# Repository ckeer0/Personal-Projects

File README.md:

# Personal-Projects
All things that don't fit into other repos.

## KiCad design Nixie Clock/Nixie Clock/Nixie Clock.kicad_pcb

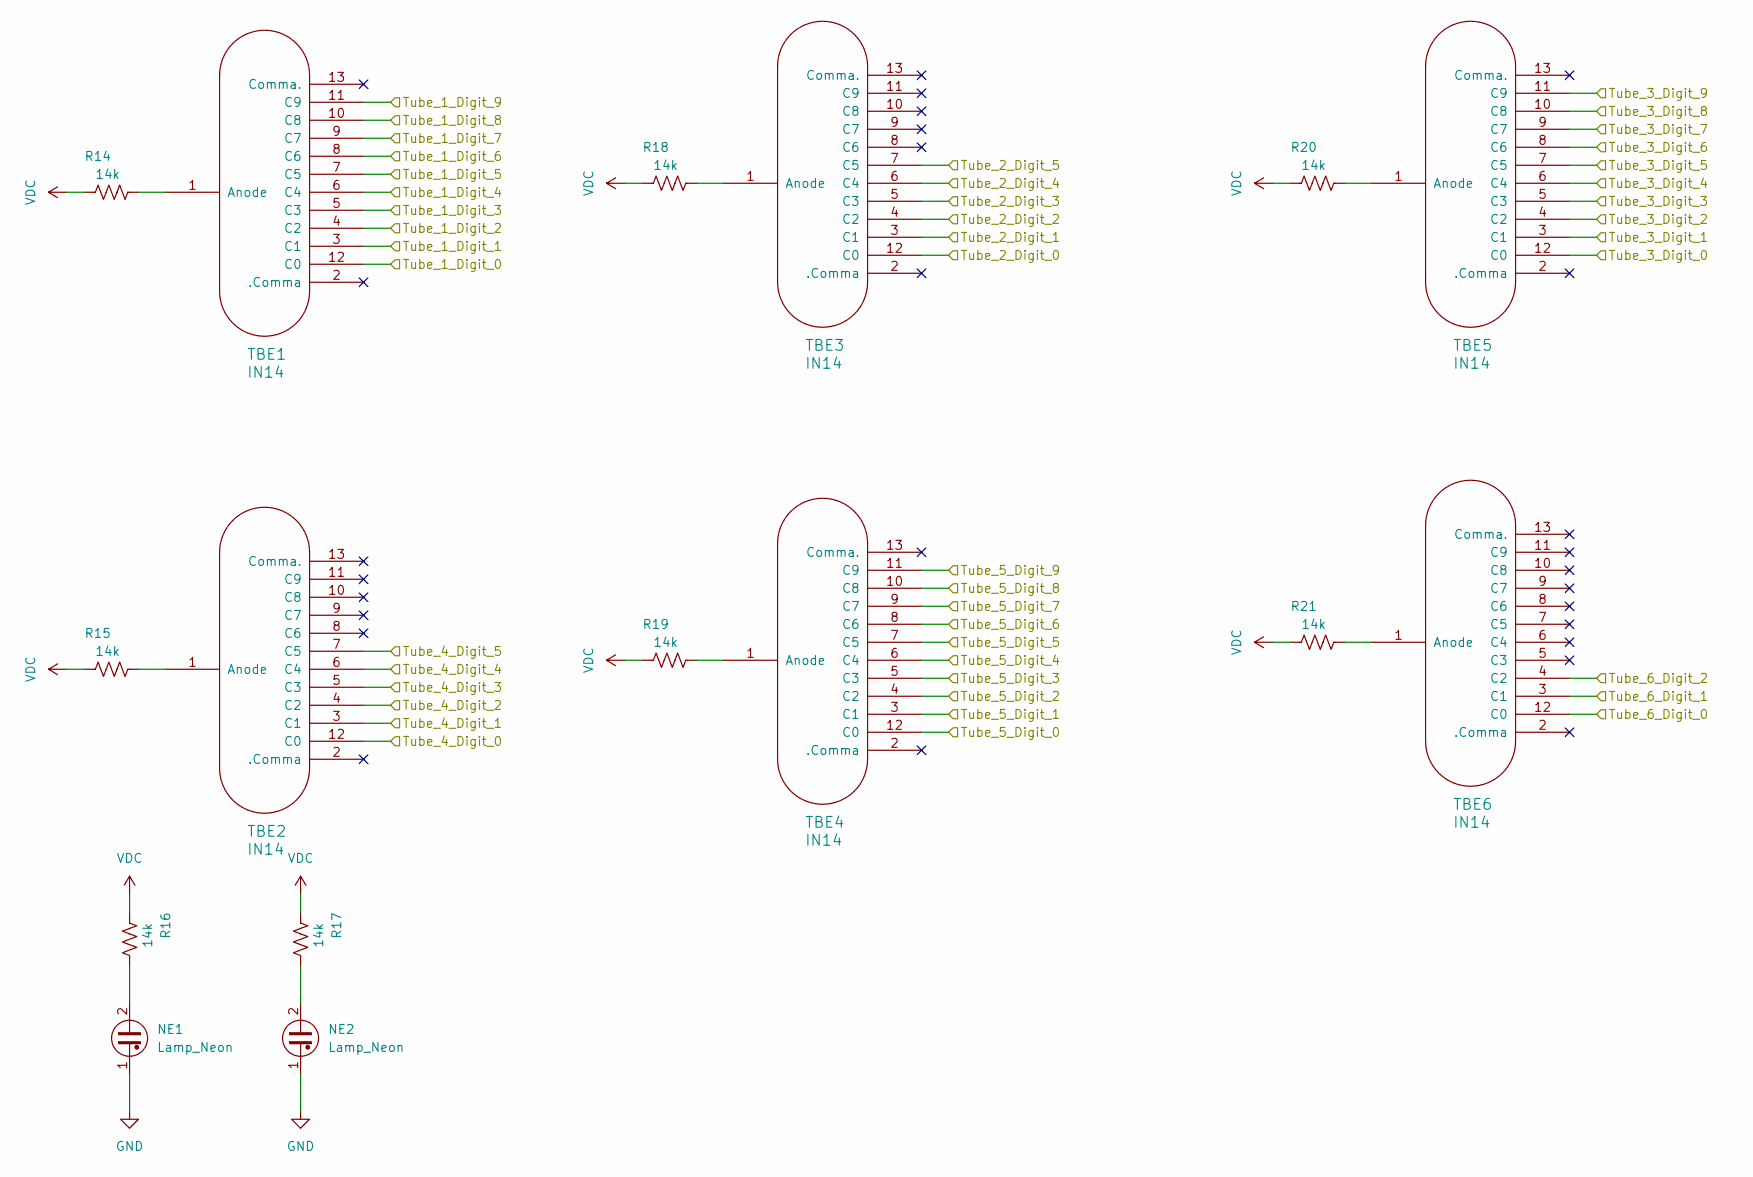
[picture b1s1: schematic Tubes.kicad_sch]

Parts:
NE1, NE2: Lamp_Neon; LED_D5.0mm_Clear
R14, R15, R18, R19, R20, R21: 14k; R_Axial_DIN0204_L3.6mm_D1.6mm_P7.62mm_Horizontal
R16, R17: 14k; R_Axial_DIN0207_L6.3mm_D2.5mm_P10.16mm_Horizontal
TBE1, TBE2, TBE3, TBE4, TBE5, TBE6: IN14; IN-14-mod

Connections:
/Tube_1_Digit_0: TBE1.12 (C0); also elsewhere on the board
/Tube_1_Digit_1: TBE1.3 (C1); also elsewhere on the board
/Tube_1_Digit_2: TBE1.4 (C2); also elsewhere on the board
/Tube_1_Digit_3: TBE1.5 (C3); also elsewhere on the board
/Tube_1_Digit_4: TBE1.6 (C4); also elsewhere on the board
/Tube_1_Digit_5: TBE1.7 (C5); also elsewhere on the board
/Tube_1_Digit_6: TBE1.8 (C6); also elsewhere on the board
/Tube_1_Digit_7: TBE1.9 (C7); also elsewhere on the board
/Tube_1_Digit_8: TBE1.10 (C8); also elsewhere on the board
/Tube_1_Digit_9: TBE1.11 (C9); also elsewhere on the board
/Tube_2_Digit_0: TBE3.12 (C0); also elsewhere on the board
/Tube_2_Digit_1: TBE3.3 (C1); also elsewhere on the board
/Tube_2_Digit_2: TBE3.4 (C2); also elsewhere on the board
/Tube_2_Digit_3: TBE3.5 (C3); also elsewhere on the board
/Tube_2_Digit_4: TBE3.6 (C4); also elsewhere on the board
/Tube_2_Digit_5: TBE3.7 (C5); also elsewhere on the board
/Tube_3_Digit_0: TBE5.12 (C0); also elsewhere on the board
/Tube_3_Digit_1: TBE5.3 (C1); also elsewhere on the board
/Tube_3_Digit_2: TBE5.4 (C2); also elsewhere on the board
/Tube_3_Digit_3: TBE5.5 (C3); also elsewhere on the board
/Tube_3_Digit_4: TBE5.6 (C4); also elsewhere on the board
/Tube_3_Digit_5: TBE5.7 (C5); also elsewhere on the board
/Tube_3_Digit_6: TBE5.8 (C6); also elsewhere on the board
/Tube_3_Digit_7: TBE5.9 (C7); also elsewhere on the board
/Tube_3_Digit_8: TBE5.10 (C8); also elsewhere on the board
/Tube_3_Digit_9: TBE5.11 (C9); also elsewhere on the board
/Tube_4_Digit_0: TBE2.12 (C0); also elsewhere on the board
/Tube_4_Digit_1: TBE2.3 (C1); also elsewhere on the board
/Tube_4_Digit_2: TBE2.4 (C2); also elsewhere on the board
/Tube_4_Digit_3: TBE2.5 (C3); also elsewhere on the board
/Tube_4_Digit_4: TBE2.6 (C4); also elsewhere on the board
/Tube_4_Digit_5: TBE2.7 (C5); also elsewhere on the board
/Tube_5_Digit_0: TBE4.12 (C0); also elsewhere on the board
/Tube_5_Digit_1: TBE4.3 (C1); also elsewhere on the board
/Tube_5_Digit_2: TBE4.4 (C2); also elsewhere on the board
/Tube_5_Digit_3: TBE4.5 (C3); also elsewhere on the board
/Tube_5_Digit_4: TBE4.6 (C4); also elsewhere on the board
/Tube_5_Digit_5: TBE4.7 (C5); also elsewhere on the board
/Tube_5_Digit_6: TBE4.8 (C6); also elsewhere on the board
/Tube_5_Digit_7: TBE4.9 (C7); also elsewhere on the board
/Tube_5_Digit_8: TBE4.10 (C8); also elsewhere on the board
/Tube_5_Digit_9: TBE4.11 (C9); also elsewhere on the board
/Tube_6_Digit_0: TBE6.12 (C0); also elsewhere on the board
/Tube_6_Digit_1: TBE6.3 (C1); also elsewhere on the board
/Tube_6_Digit_2: TBE6.4 (C2); also elsewhere on the board
GND: NE1.1, NE2.1; also elsewhere on the board
unnamed: NE1.2, R16.1
unnamed: NE2.2, R17.1
unnamed: R14.1, TBE1.1 (Anode)
unnamed: R15.1, TBE2.1 (Anode)
unnamed: R18.1, TBE3.1 (Anode)
unnamed: R19.1, TBE4.1 (Anode)
unnamed: R20.1, TBE5.1 (Anode)
unnamed: R21.1, TBE6.1 (Anode)
VDC: R14.2, R15.2, R16.2, R17.2, R18.2, R19.2, R20.2, R21.2; also elsewhere on the board

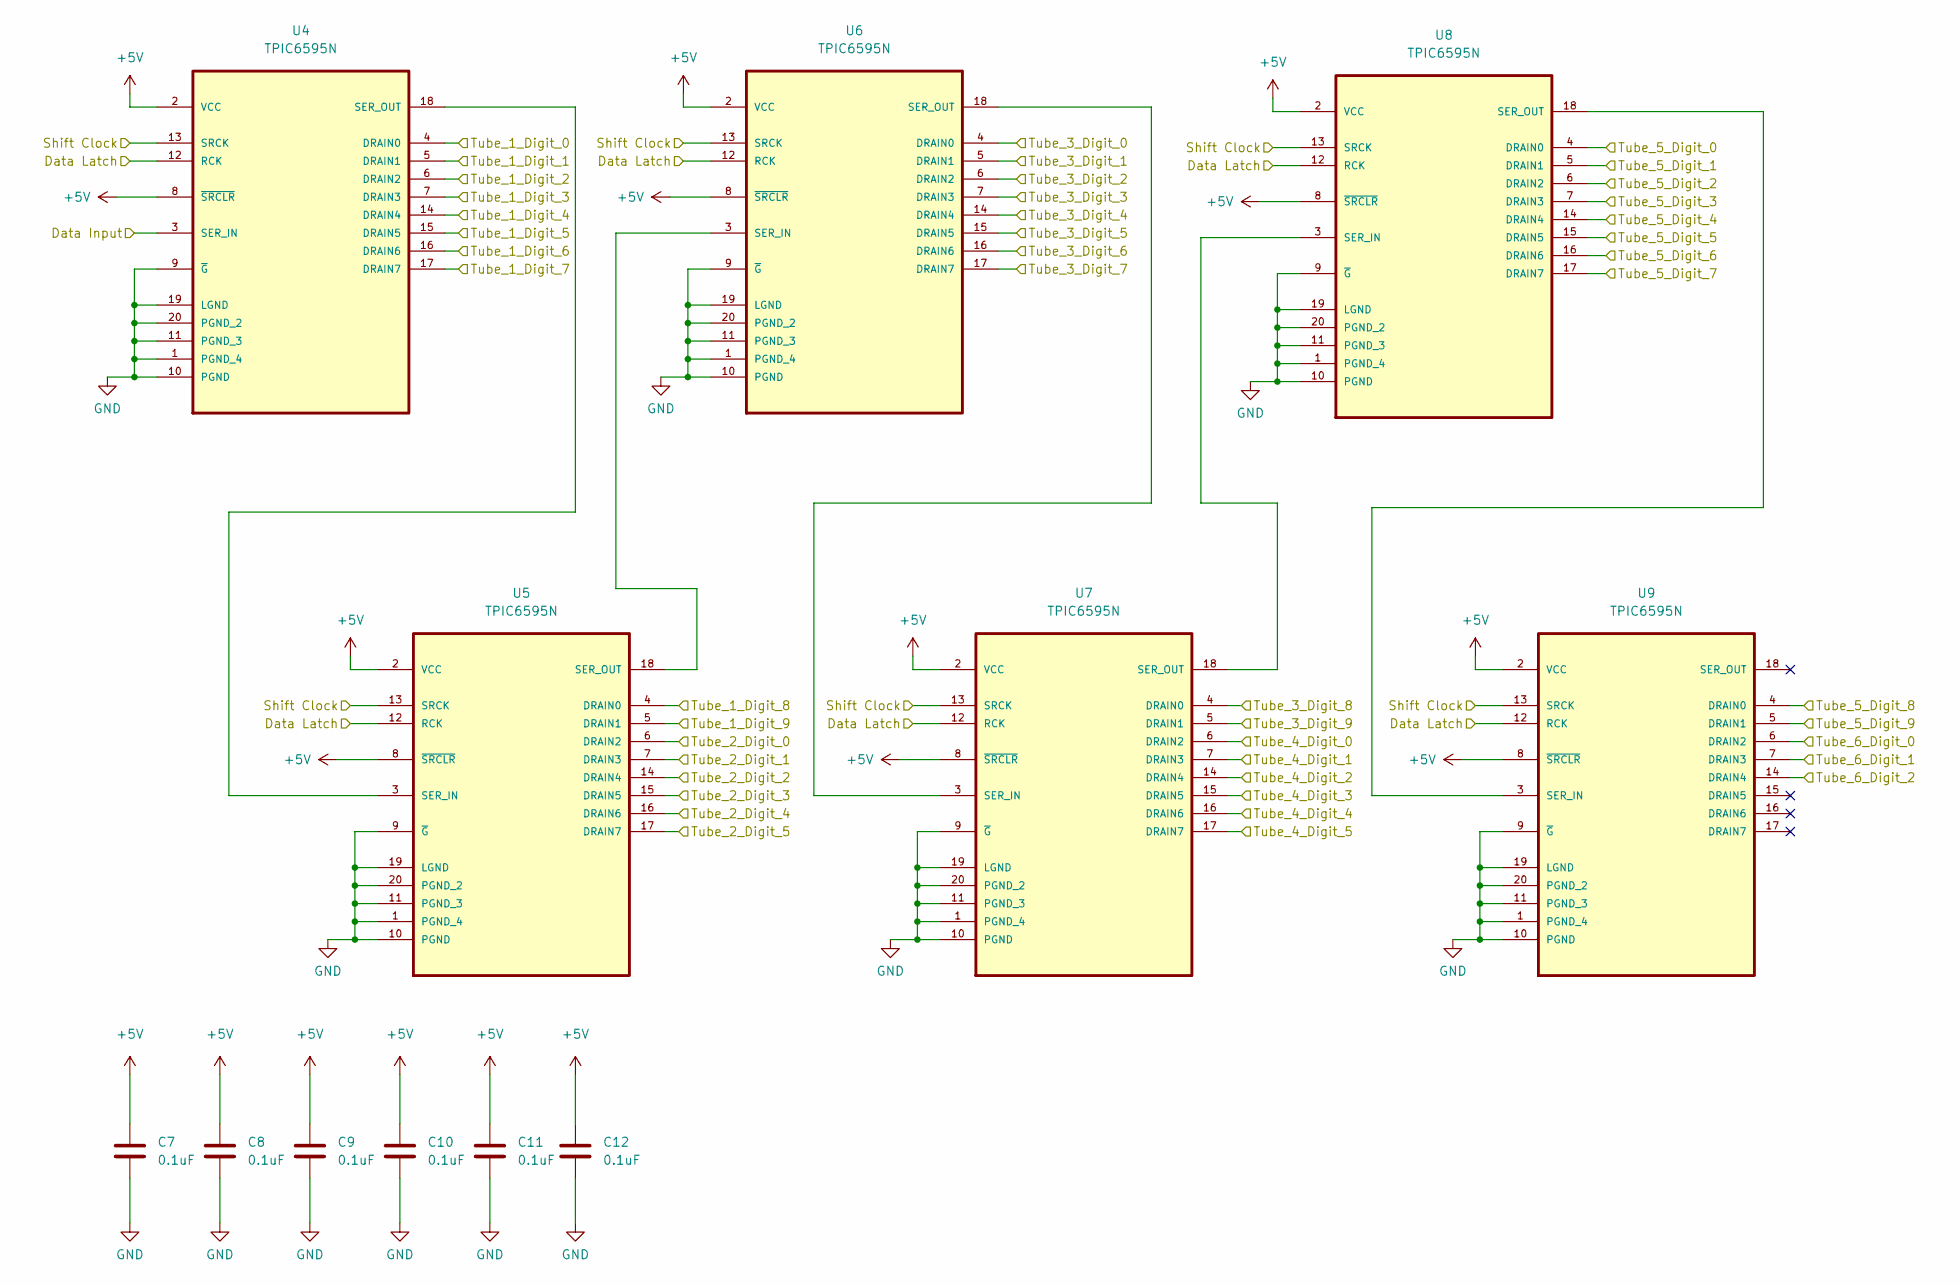
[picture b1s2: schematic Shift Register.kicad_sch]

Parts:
C7, C8, C9, C10, C11, C12: 0.1uF; CP_Radial_D4.0mm_P1.50mm
U4, U5, U6, U7, U8, U9: TPIC6595N; DIP254P762X508-20; MPN TPIC6595N

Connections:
+5V: C7.1, C8.1, C9.1, C10.1, C11.1, C12.1, U4.2 (VCC), U4.8 (~SRCLR), U5.2 (VCC), U5.8 (~SRCLR), U6.2 (VCC), U6.8 (~SRCLR), U7.2 (VCC), U7.8 (~SRCLR), U8.2 (VCC), U8.8 (~SRCLR), U9.2 (VCC), U9.8 (~SRCLR); also elsewhere on the board
/Data Latch: U4.12 (RCK), U5.12 (RCK), U6.12 (RCK), U7.12 (RCK), U8.12 (RCK), U9.12 (RCK); also elsewhere on the board
/Data Output: U4.3 (SER_IN); also elsewhere on the board
/Shift Clock: U4.13 (SRCK), U5.13 (SRCK), U6.13 (SRCK), U7.13 (SRCK), U8.13 (SRCK), U9.13 (SRCK); also elsewhere on the board
/Tube_1_Digit_0: U4.4 (DRAIN0); also elsewhere on the board
/Tube_1_Digit_1: U4.5 (DRAIN1); also elsewhere on the board
/Tube_1_Digit_2: U4.6 (DRAIN2); also elsewhere on the board
/Tube_1_Digit_3: U4.7 (DRAIN3); also elsewhere on the board
/Tube_1_Digit_4: U4.14 (DRAIN4); also elsewhere on the board
/Tube_1_Digit_5: U4.15 (DRAIN5); also elsewhere on the board
/Tube_1_Digit_6: U4.16 (DRAIN6); also elsewhere on the board
/Tube_1_Digit_7: U4.17 (DRAIN7); also elsewhere on the board
/Tube_1_Digit_8: U5.4 (DRAIN0); also elsewhere on the board
/Tube_1_Digit_9: U5.5 (DRAIN1); also elsewhere on the board
/Tube_2_Digit_0: U5.6 (DRAIN2); also elsewhere on the board
/Tube_2_Digit_1: U5.7 (DRAIN3); also elsewhere on the board
/Tube_2_Digit_2: U5.14 (DRAIN4); also elsewhere on the board
/Tube_2_Digit_3: U5.15 (DRAIN5); also elsewhere on the board
/Tube_2_Digit_4: U5.16 (DRAIN6); also elsewhere on the board
/Tube_2_Digit_5: U5.17 (DRAIN7); also elsewhere on the board
/Tube_3_Digit_0: U6.4 (DRAIN0); also elsewhere on the board
/Tube_3_Digit_1: U6.5 (DRAIN1); also elsewhere on the board
/Tube_3_Digit_2: U6.6 (DRAIN2); also elsewhere on the board
/Tube_3_Digit_3: U6.7 (DRAIN3); also elsewhere on the board
/Tube_3_Digit_4: U6.14 (DRAIN4); also elsewhere on the board
/Tube_3_Digit_5: U6.15 (DRAIN5); also elsewhere on the board
/Tube_3_Digit_6: U6.16 (DRAIN6); also elsewhere on the board
/Tube_3_Digit_7: U6.17 (DRAIN7); also elsewhere on the board
/Tube_3_Digit_8: U7.4 (DRAIN0); also elsewhere on the board
/Tube_3_Digit_9: U7.5 (DRAIN1); also elsewhere on the board
/Tube_4_Digit_0: U7.6 (DRAIN2); also elsewhere on the board
/Tube_4_Digit_1: U7.7 (DRAIN3); also elsewhere on the board
/Tube_4_Digit_2: U7.14 (DRAIN4); also elsewhere on the board
/Tube_4_Digit_3: U7.15 (DRAIN5); also elsewhere on the board
/Tube_4_Digit_4: U7.16 (DRAIN6); also elsewhere on the board
/Tube_4_Digit_5: U7.17 (DRAIN7); also elsewhere on the board
/Tube_5_Digit_0: U8.4 (DRAIN0); also elsewhere on the board
/Tube_5_Digit_1: U8.5 (DRAIN1); also elsewhere on the board
/Tube_5_Digit_2: U8.6 (DRAIN2); also elsewhere on the board
/Tube_5_Digit_3: U8.7 (DRAIN3); also elsewhere on the board
/Tube_5_Digit_4: U8.14 (DRAIN4); also elsewhere on the board
/Tube_5_Digit_5: U8.15 (DRAIN5); also elsewhere on the board
/Tube_5_Digit_6: U8.16 (DRAIN6); also elsewhere on the board
/Tube_5_Digit_7: U8.17 (DRAIN7); also elsewhere on the board
/Tube_5_Digit_8: U9.4 (DRAIN0); also elsewhere on the board
/Tube_5_Digit_9: U9.5 (DRAIN1); also elsewhere on the board
/Tube_6_Digit_0: U9.6 (DRAIN2); also elsewhere on the board
/Tube_6_Digit_1: U9.7 (DRAIN3); also elsewhere on the board
/Tube_6_Digit_2: U9.14 (DRAIN4); also elsewhere on the board
GND: C7.2, C8.2, C9.2, C10.2, C11.2, C12.2, U4.1 (PGND_4), U4.9 (~G), U4.10 (PGND), U4.11 (PGND_3), U4.19 (LGND), U4.20 (PGND_2), U5.1 (PGND_4), U5.9 (~G), U5.10 (PGND), U5.11 (PGND_3), U5.19 (LGND), U5.20 (PGND_2), U6.1 (PGND_4), U6.9 (~G), U6.10 (PGND), U6.11 (PGND_3), U6.19 (LGND), U6.20 (PGND_2), U7.1 (PGND_4), U7.9 (~G), U7.10 (PGND), U7.11 (PGND_3), U7.19 (LGND), U7.20 (PGND_2), U8.1 (PGND_4), U8.9 (~G), U8.10 (PGND), U8.11 (PGND_3), U8.19 (LGND), U8.20 (PGND_2), U9.1 (PGND_4), U9.9 (~G), U9.10 (PGND), U9.11 (PGND_3), U9.19 (LGND), U9.20 (PGND_2); also elsewhere on the board
unnamed: U4.18 (SER_OUT), U5.3 (SER_IN)
unnamed: U5.18 (SER_OUT), U6.3 (SER_IN)
unnamed: U6.18 (SER_OUT), U7.3 (SER_IN)
unnamed: U7.18 (SER_OUT), U8.3 (SER_IN)
unnamed: U8.18 (SER_OUT), U9.3 (SER_IN)

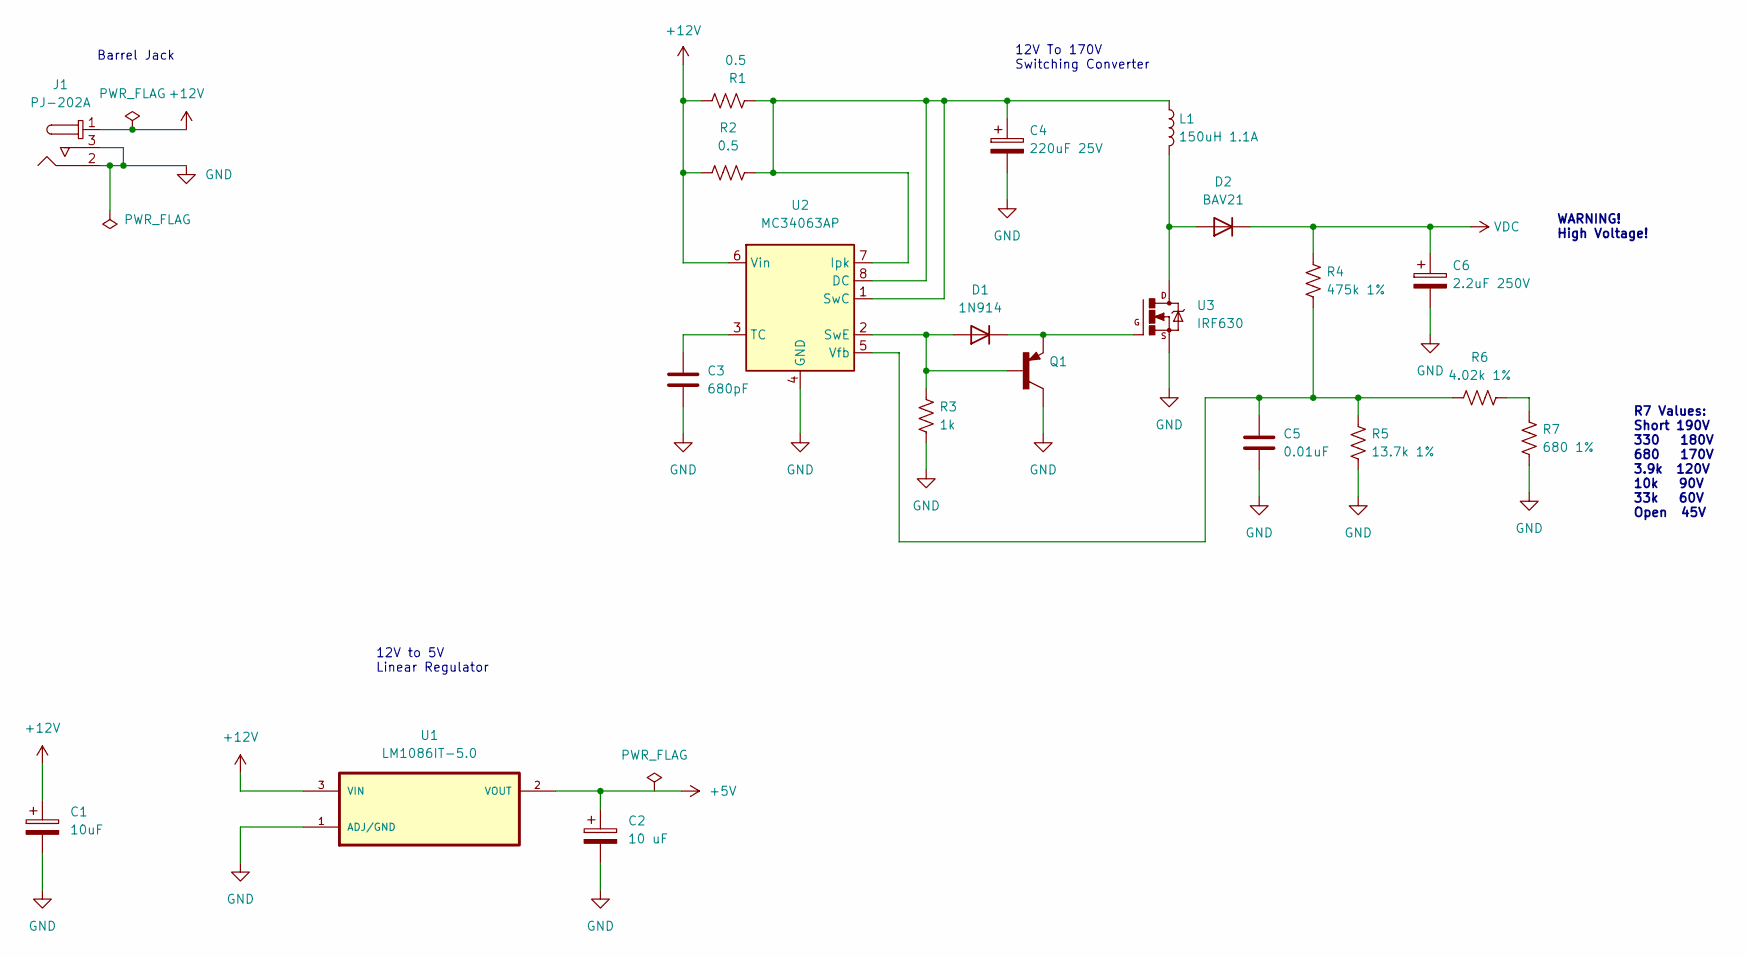
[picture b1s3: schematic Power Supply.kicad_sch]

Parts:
C1: 10uF; CP_Radial_D6.3mm_P2.50mm
C2: 10 uF; CP_Radial_D6.3mm_P2.50mm
C3: 680pF; C_Disc_D3.8mm_W2.6mm_P2.50mm
C4: 220uF 25V; CP_Radial_D8.0mm_P3.50mm
C5: 0.01uF; C_Disc_D5.1mm_W3.2mm_P5.00mm
C6: 2.2uF 250V; CP_Radial_D6.3mm_P2.50mm
D1: 1N914; D_DO-35_SOD27_P7.62mm_Horizontal
D2: BAV21; D_DO-35_SOD27_P7.62mm_Horizontal
J1: PJ-202A; Barrel_Jack_5.5mmODx2.1mmID_PJ-202A; MPN PJ-202A; Digi-Key_PN CP-202A-ND
L1: 150uH 1.1A; L_Radial_D21.0mm_P19.00mm
Q1: PARTREV 2
R1, R2: 0.5; R_Axial_DIN0414_L11.9mm_D4.5mm_P15.24mm_Horizontal
R3: 1k; R_Axial_DIN0207_L6.3mm_D2.5mm_P10.16mm_Horizontal
R4: 475k 1%; R_Axial_DIN0204_L3.6mm_D1.6mm_P7.62mm_Horizontal
R5: 13.7k 1%; R_Axial_DIN0207_L6.3mm_D2.5mm_P10.16mm_Horizontal
R6: 4.02k 1%; R_Axial_DIN0204_L3.6mm_D1.6mm_P7.62mm_Horizontal
R7: 680 1%; R_Axial_DIN0207_L6.3mm_D2.5mm_P10.16mm_Horizontal
U1: LM1086IT-5.0; TO254P1054X470X1955-3
U2: MC34063AP; DIP-8_W7.62mm
U3: IRF630; TO-220-3_Vertical

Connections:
+5V: C2.1, U1.2 (VOUT); also elsewhere on the board
+12V: C1.1, J1.1, R1.1, R2.1, U1.3 (VIN), U2.6 (Vin); also elsewhere on the board
GND: C1.2, C2.2, C3.2, C4.2, C5.2, C6.2, J1.2, J1.3, Q1.3, R3.2, R5.2, R7.2, U1.1 (ADJ/GND), U2.4 (GND), U3.3; also elsewhere on the board
unnamed: C3.1, U2.3 (TC)
unnamed: C4.1, L1.1, R1.2, R2.2, U2.1 (SwC), U2.7 (Ipk), U2.8 (DC)
unnamed: C5.1, R4.2, R5.1, R6.2, U2.5 (Vfb)
unnamed: D1.1 (K), Q1.1, U3.1
unnamed: D1.2 (A), Q1.2, R3.1, U2.2 (SwE)
unnamed: D2.2 (A), L1.2, U3.2
unnamed: R6.1, R7.1
VDC: C6.1, D2.1 (K), R4.1; also elsewhere on the board

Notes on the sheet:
Barrel Jack
R7 Values: Short 190V 330 180V 680 170V 3.9k 120V 10k 90V 33k 60V Open 45V
12V to 5V Linear Regulator
12V To 170V Switching Converter
WARNING! High Voltage!

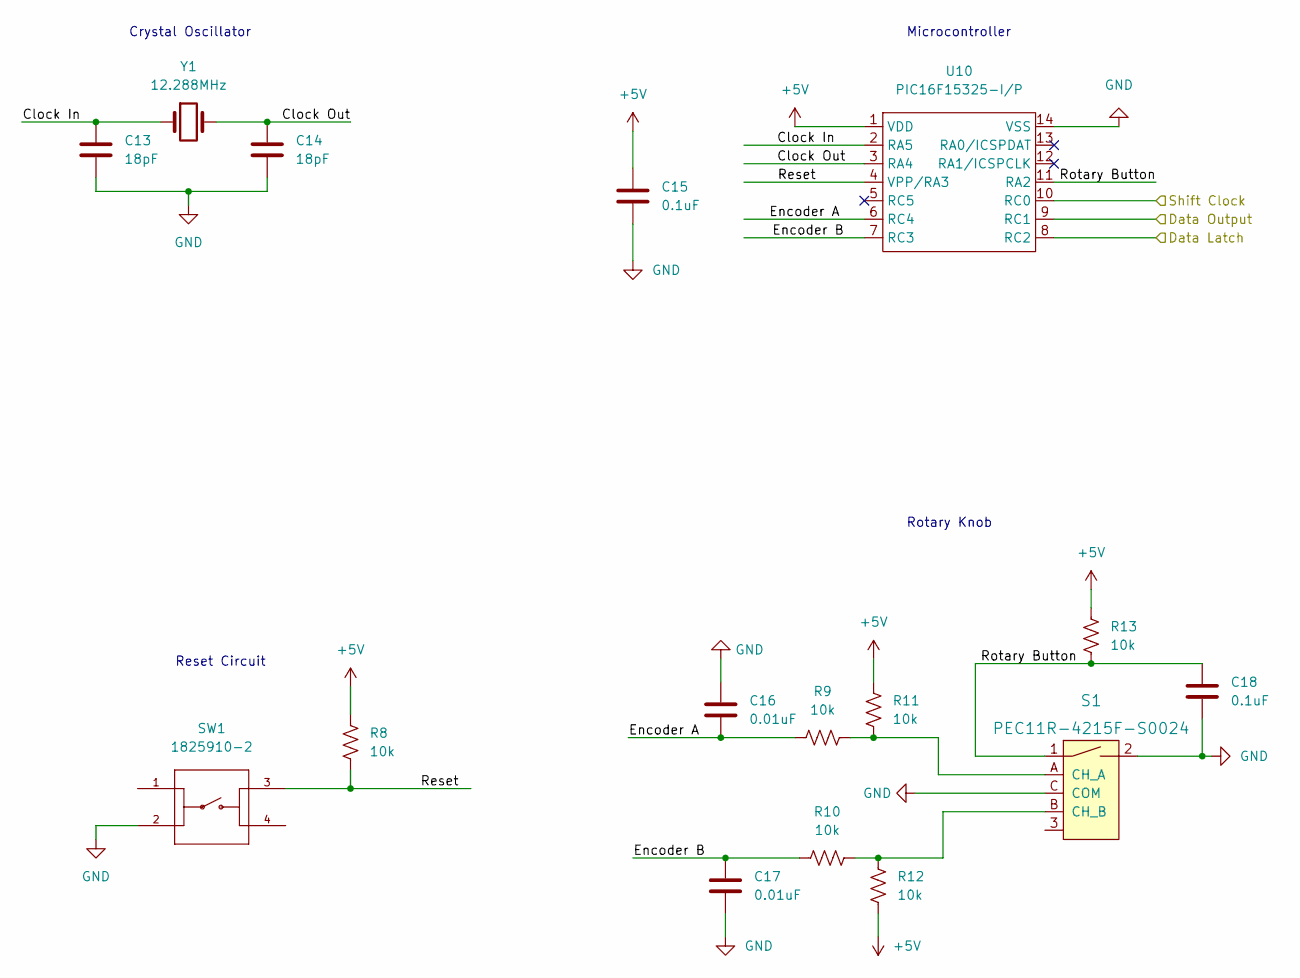
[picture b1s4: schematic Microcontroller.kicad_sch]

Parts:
C13, C14: 18pF; C_Disc_D5.0mm_W2.5mm_P2.50mm
C15, C18: 0.1uF; CP_Radial_D4.0mm_P1.50mm
C16, C17: 0.01uF; C_Disc_D5.1mm_W3.2mm_P5.00mm
R8, R9, R10, R11, R12, R13: 10k; R_Axial_DIN0309_L9.0mm_D3.2mm_P12.70mm_Horizontal
S1: PEC11R-4215F-S0024; Rotary_Encoder_Switched_PEC11R; MPN PEC11R-4215F-S0024; Digi-Key_PN PEC11R-4215F-S0024-ND
SW1: 1825910-2; TE_1825910-2
U10: PIC16F15325-I/P; DIP-14_W7.62mm
Y1: 12.288MHz; Crystal_HC49-4H_Vertical

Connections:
+5V: C15.1, R8.1, R11.2, R12.1, R13.2, U10.1 (VDD); also elsewhere on the board
/Data Latch: U10.8 (RC2); also elsewhere on the board
/Data Output: U10.9 (RC1); also elsewhere on the board
/Microcontroller/Clock In: C13.1, U10.2 (RA5), Y1.1
/Microcontroller/Clock Out: C14.1, U10.3 (RA4), Y1.2
/Microcontroller/Encoder A: C16.2, R9.1, U10.6 (RC4)
/Microcontroller/Encoder B: C17.1, R10.1, U10.7 (RC3)
/Microcontroller/Reset: R8.2, SW1.3, U10.4 (VPP/RA3)
/Microcontroller/Rotary Button: C18.1, R13.1, S1.1, U10.11 (RA2)
/Shift Clock: U10.10 (RC0); also elsewhere on the board
GND: C13.2, C14.2, C15.2, C16.1, C17.2, C18.2, S1.2, S1.C (COM), SW1.2, U10.14 (VSS); also elsewhere on the board
unnamed: R10.2, R12.2, S1.B (CH_B)
unnamed: R9.2, R11.1, S1.A (CH_A)

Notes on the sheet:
Microcontroller
Reset Circuit
Rotary Knob
Crystal Oscillator

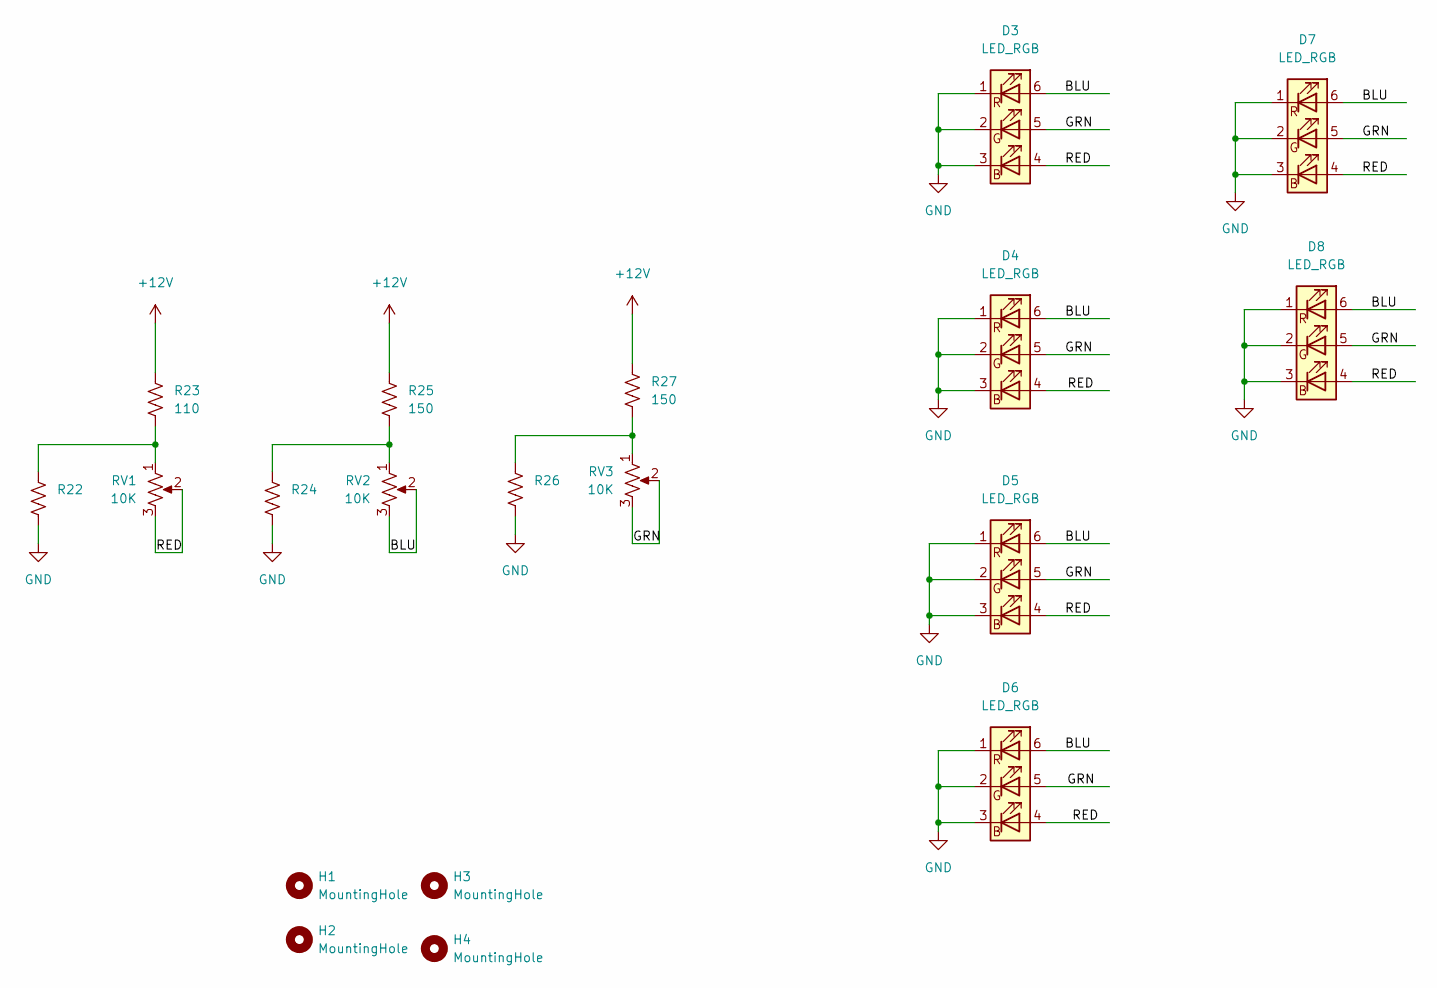
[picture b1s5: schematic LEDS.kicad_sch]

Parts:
D3, D4, D5, D6, D7, D8: LED_RGB; CLY6D-FKC-CK1N1D1BB7D3D3
H1, H2, H3, H4: MountingHole; MountingHole_4.3mm_M4
R22, R24, R26: Resistor_THT:R_Axial_DIN0207_L6.3mm_D2.5mm_P10.16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; R_Axial_DIN0207_L6.3mm_D2.5mm_P10.16mm_Horizontal
R23: 110; R_Axial_DIN0411_L9.9mm_D3.6mm_P12.70mm_Horizontal
R25, R27: 150; R_Axial_DIN0414_L11.9mm_D4.5mm_P15.24mm_Horizontal
RV1, RV2, RV3: 10K; WH148

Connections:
+12V: R23.1, R25.1, R27.1; also elsewhere on the board
/LEDS/BLU: D3.6 (RA), D4.6 (RA), D5.6 (RA), D6.6 (RA), D7.6 (RA), D8.6 (RA), RV2.2, RV2.3
/LEDS/GRN: D3.5 (GA), D4.5 (GA), D5.5 (GA), D6.5 (GA), D7.5 (GA), D8.5 (GA), RV3.2, RV3.3
/LEDS/RED: D3.4 (BA), D4.4 (BA), D5.4 (BA), D6.4 (BA), D7.4 (BA), D8.4 (BA), RV1.2, RV1.3
GND: D3.1 (RK), D3.2 (GK), D3.3 (BK), D4.1 (RK), D4.2 (GK), D4.3 (BK), D5.1 (RK), D5.2 (GK), D5.3 (BK), D6.1 (RK), D6.2 (GK), D6.3 (BK), D7.1 (RK), D7.2 (GK), D7.3 (BK), D8.1 (RK), D8.2 (GK), D8.3 (BK), R22.2, R24.2, R26.2; also elsewhere on the board
unnamed: R22.1, R23.2, RV1.1
unnamed: R24.1, R25.2, RV2.1
unnamed: R26.1, R27.2, RV3.1

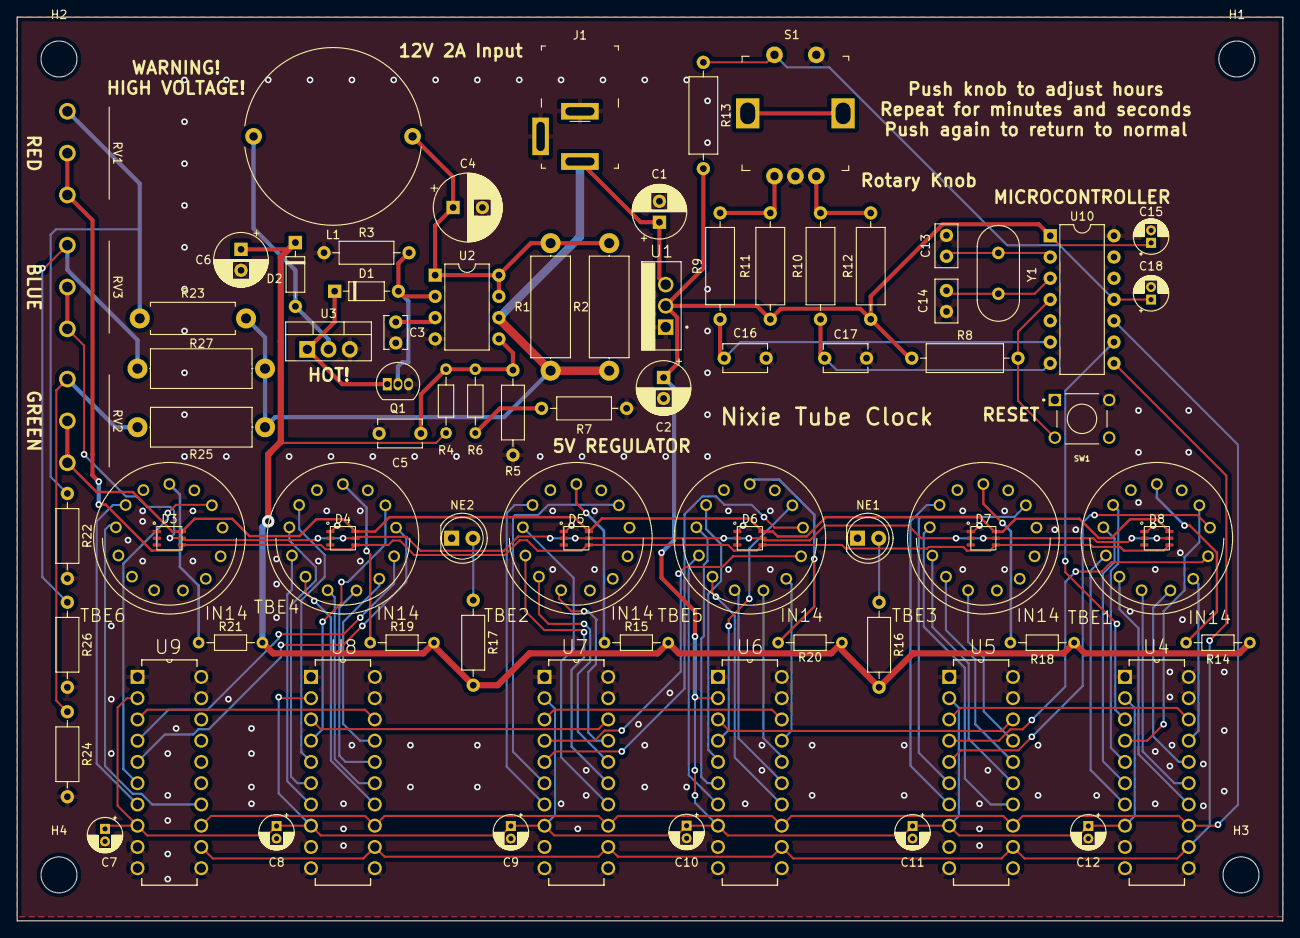
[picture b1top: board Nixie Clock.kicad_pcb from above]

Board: 2 copper layers, 151.2 x 108.0 mm, 84 parts (0 on the bottom side), 86 nets.

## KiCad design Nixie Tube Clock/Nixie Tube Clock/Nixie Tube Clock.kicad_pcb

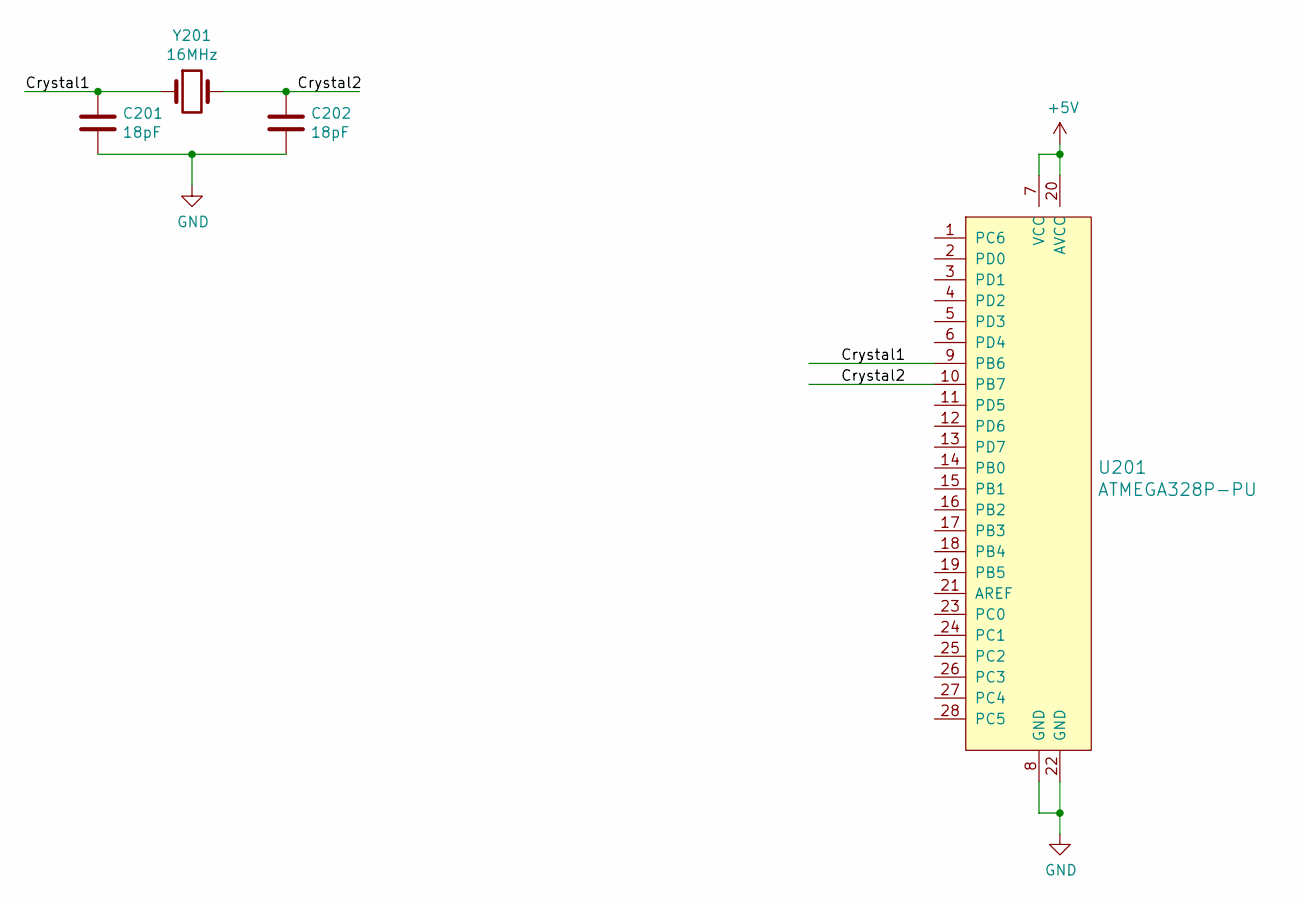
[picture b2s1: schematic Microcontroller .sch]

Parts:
C201, C202: 18pF; C_Disc_D3.8mm_W2.6mm_P2.50mm
U201: ATMEGA328P-PU; DIP-28_W7.62mm; MPN ATMEGA328P-PU; Digi-Key_PN ATMEGA328P-PU-ND
Y201: 16MHz; Resonator-2Pin_W10.0mm_H5.0mm

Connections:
+5V: U201.7 (VCC), U201.20 (AVCC)
/Microcontroller/Crystal1: C201.1, U201.9 (PB6), Y201.1
/Microcontroller/Crystal2: C202.1, U201.10 (PB7), Y201.2
GND: C201.2, C202.2, U201.8 (GND), U201.22 (GND)

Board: 2 copper layers, 4 parts (0 on the bottom side), 4 nets, no tracks yet.

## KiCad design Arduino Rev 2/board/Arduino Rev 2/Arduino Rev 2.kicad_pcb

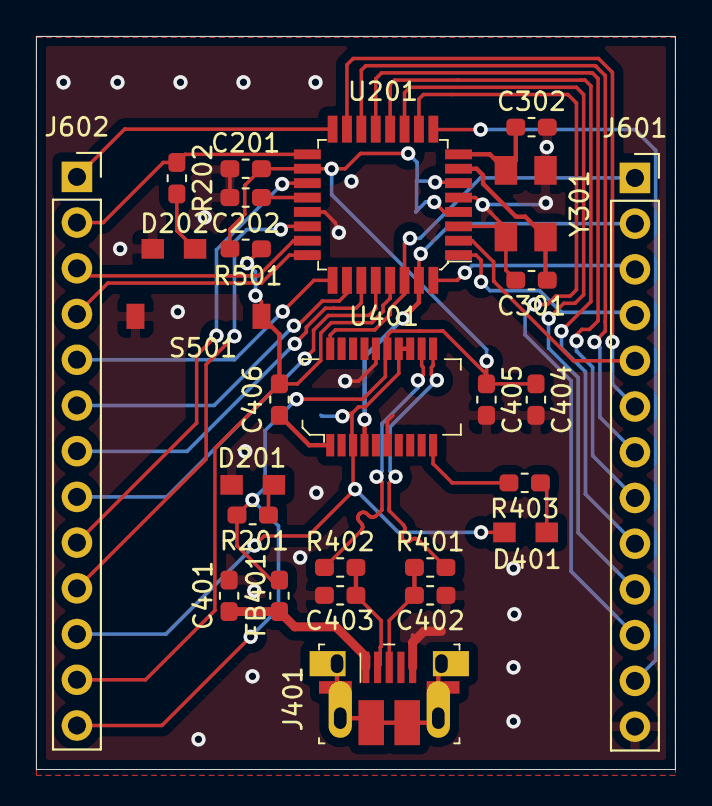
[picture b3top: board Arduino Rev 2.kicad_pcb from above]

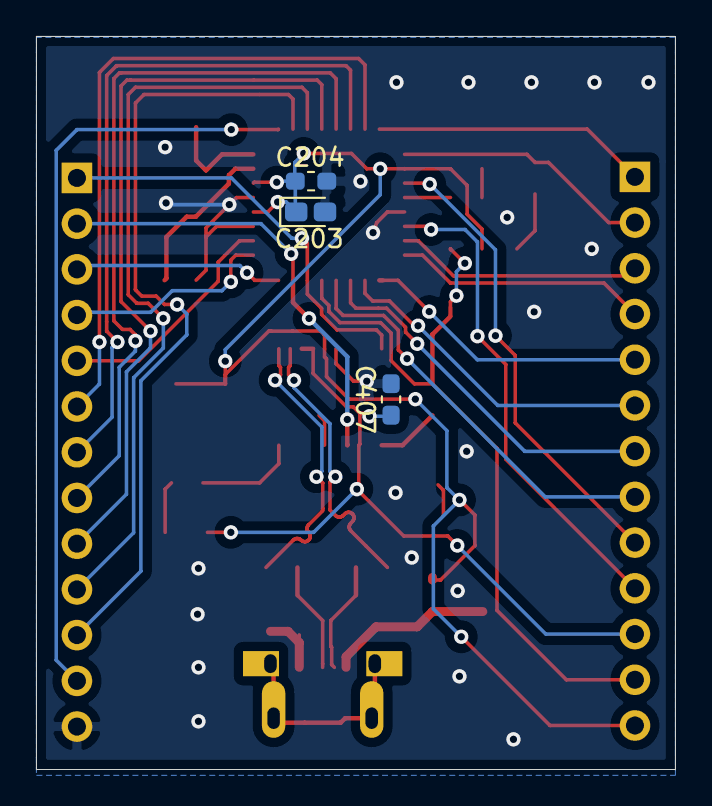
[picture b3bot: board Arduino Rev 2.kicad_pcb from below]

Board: 2 copper layers, 35.5 x 40.7 mm, 30 parts (3 on the bottom side), 39 nets.

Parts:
C201, C202, C204, C406: 100 nF; C_0603_1608Metric_Pad1.05x0.95mm_HandSolder
C203: 4.7 uF; CP_EIA-1608-10_AVX-L_Pad1.25x1.05mm_HandSolder
C301, C302: 22pF; C_0603_1608Metric_Pad1.05x0.95mm_HandSolder
C401: 10nF; C_0603_1608Metric_Pad1.05x0.95mm_HandSolder
C402, C403: 47pF; C_0603_1608Metric_Pad1.05x0.95mm_HandSolder
C404, C407: 100nF; C_0603_1608Metric_Pad1.05x0.95mm_HandSolder
C405: 4.7uF; C_0603_1608Metric_Pad1.05x0.95mm_HandSolder
D201, D202, D401: LED; led
FB401: 600 OHM @100MHz; R_0603_1608Metric_Pad1.05x0.95mm_HandSolder
J401: 10103594-0001LF; USB_Micro_B_Female_10103594-0001LF
J601, J602: Conn_01x12_Female; PinSocket_1x13_P2.54mm_Vertical
R201, R202, R501: R_US; R_0603_1608Metric_Pad1.05x0.95mm_HandSolder
R401, R402: 27OHM; R_0603_1608Metric_Pad1.05x0.95mm_HandSolder
R403: 270 OHM; R_0603_1608Metric_Pad1.05x0.95mm_HandSolder
S501: GPTS203211B; button
U201: ATMEGA328-AU; TQFP-32_7x7mm
U401: FT231XS-U; SSOP-20_W3.9mm
Y301: ECS-160-20-30B-AGL-TR

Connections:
+3V3: C407.1, D401.2, J602.11, U401.3, U401.13, U401.14
+5V: C201.2, C203.1, C204.2, C404.1, C405.1, FB401.1, J602.13, R201.1, R501.1, U201.4, U201.6, U201.18, U401.15
/ATMega328/AREF: C202.1, U201.20
/ATMega328/XTAL1: C301.1, U201.7, Y301.1
/ATMega328/XTAL2: C302.1, U201.8, Y301.3
/D0_RX: J601.1, U201.30, U401.20
/D1_TX: J601.2, U201.31, U401.4
/PIN HEADERS/3: J601.3, U201.32
/PIN HEADERS/4: J601.4, U201.1
/PIN HEADERS/5: J601.5, U201.2
/PIN HEADERS/6: J601.12, U201.9
/PIN HEADERS/7: J601.11, U201.10
/PIN HEADERS/8: J601.10, U201.11
/PIN HEADERS/9: J601.9, U201.12
/PIN HEADERS/10: J601.8, U201.13
/PIN HEADERS/11: J601.7, U201.14
/PIN HEADERS/12: J601.6, U201.15
/PIN HEADERS/13: J602.1, U201.16
/PIN HEADERS/14: J602.2, R202.1, U201.17
/PIN HEADERS/15: J602.3, U201.23
/PIN HEADERS/16: J602.4, U201.24
/PIN HEADERS/17: J602.5, U201.25
/PIN HEADERS/18: J602.6, U201.26
/PIN HEADERS/19: J602.7, U201.27
/PIN HEADERS/20: J602.8, U201.28
/PIN HEADERS/21: J602.9, U201.19
/PIN HEADERS/22: J602.10, U201.22
/RESET: C406.1, J602.12, R501.2, S501.2, U201.29
/USB TO UART/D+: C402.1, J401.3, R401.2
/USB TO UART/D-: C403.1, J401.2, R402.2
/USB TO UART/d2+: R401.1, U401.11
/USB TO UART/d2-: R402.1, U401.12
GND: C201.1, C202.2, C203.2, C204.1, C301.2, C302.2, C401.1, C402.2, C403.2, C404.2, C405.2, C407.2, D201.1, D202.1, J401.5, J601.13, S501.1, U201.3, U201.5, U201.21, U401.6, U401.16, Y301.2, Y301.4
unnamed: C401.2, FB401.2, J401.1
unnamed: C406.2, U401.1
unnamed: D201.2, R201.2
unnamed: D202.2, R202.2
unnamed: D401.1, R403.1
unnamed: R403.2, U401.10

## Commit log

2020-07-13 Initial Commit for board
2020-07-13 Minor Restructure
2020-07-13 Added MCU, USB, and Reset Page
2020-07-14 finished Schematic
2020-07-15 Fixed Schematic. Routing Finished
2020-07-15 Added Gerbers
2020-07-16 Final Board Design
2020-07-24 Added Crystal and a few pinouts
2020-07-26 Another Commit
2020-08-18 Added this for a test.
2021-06-09 Added Initial Files
2021-12-12 Initial Files Added
2022-01-14 Atlas Test Stand
2022-04-08 Started on the Nixie Clock
2022-04-10 More Nixie Stuff
2022-04-10 Need to add footprints for passives
2022-04-11 Started Routing
2022-04-13 Mostly finished Nixie Tube Project
2022-06-30 Stuff
2022-07-28 Nixie
2022-09-14 Added additional parts
2022-10-01 Added Untitled Diagram.drawio
2022-10-01 Plumbob Use Case
2022-10-01 Added Ground Station Use Case
2022-10-09 Added DFD-0
2022-10-09 Started Level 1 DFD
2022-12-15 Ground Station Diagram
2022-12-15 Edit
2023-01-11 Avionics Diagram
2023-02-15 Update Ground Station Use Case
2023-06-15 Test Stand Block Diagram
2023-06-15 First draft
